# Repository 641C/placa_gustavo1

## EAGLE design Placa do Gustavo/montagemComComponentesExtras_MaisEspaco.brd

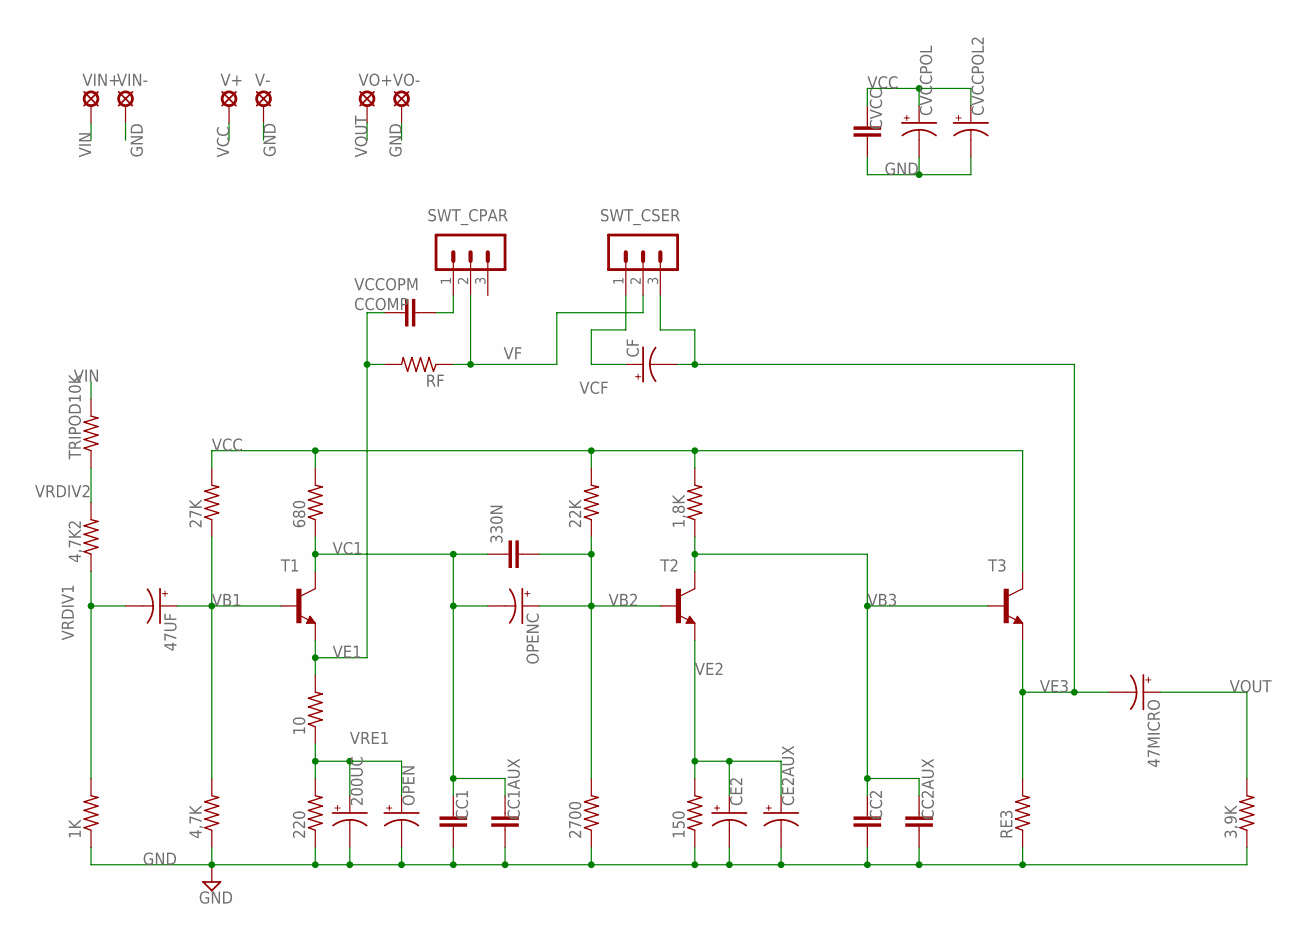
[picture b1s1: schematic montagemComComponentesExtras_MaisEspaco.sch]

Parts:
1,8K, 1K, 3,9K, 4,7K, 4,7K2, 10, 22K, 27K, 150, 220, 680, 2700: R-US_0207/10; 0207/10
47MICRO, 47UF, 200UC: CPOL-USE2.5-6; E2,5-6
330N: C-EU050-030X075; C050-030X075
CC1, CC1AUX, CC2, CC2AUX: C-EU050-030X075; C050-030X075
CCOMP: C-EU050-030X075; C050-030X075
CE2: CPOL-USE2.5-6; E2,5-6
CE2AUX: CPOL-USE5-8.5; E5-8,5
CF: CPOL-USE2.5-6; E2,5-6
CVCC: C-EU050-030X075; C050-030X075
CVCCPOL: CPOL-USE2.5-6; E2,5-6
CVCCPOL2: CPOL-USE5-8.5; E5-8,5
OPEN: CPOL-USE5-8.5; E5-8,5
OPENC: CPOL-USE2.5-6; E2,5-6
RE3: R-US_0207/10; 0207/10
RF: R-US_0207/10; 0207/10
SWT_CPAR: MA03-1
SWT_CSER: MA03-1
T1, T2, T3: BC368-NPN-TO92-ECB; TO92-ECB
TRIPOD10K: R-US_0207/10; 0207/10
V+: LSP10
V-: LSP10
VIN+: LSP10
VIN-: LSP10
VO+: LSP10
VO-: LSP10

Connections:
GND: 1K.1, 3,9K.1, 4,7K.1, 150.1, 200UC.-, 220.1, 2700.1, CC1.2, CC1AUX.2, CC2.2, CC2AUX.2, CE2.-, CE2AUX.-, CVCC.2, CVCCPOL.-, CVCCPOL2.-, OPEN.-, RE3.1, V-.MP, VIN-.MP, VO-.MP
VB1: 4,7K.2, 27K.1, 47UF.+, T1.B
VB2: 22K.1, 330N.2, 2700.2, OPENC.+, T2.B
VB3: 1,8K.1, CC2.1, CC2AUX.1, T2.C, T3.B
VC1: 330N.1, 680.1, CC1.1, CC1AUX.1, OPENC.-, T1.C
VCC: 1,8K.2, 22K.2, 27K.2, 680.2, CVCC.1, CVCCPOL.+, CVCCPOL2.+, T3.C, V+.MP
VCCOPM: CCOMP.2, SWT_CPAR.1
VCF: CF.+, SWT_CSER.1
VE1: 10.2, CCOMP.1, RF.2, T1.E
VE2: 150.2, CE2.+, CE2AUX.+, T2.E
VE3: 47MICRO.-, CF.-, RE3.2, SWT_CSER.3, T3.E
VF: RF.1, SWT_CPAR.2, SWT_CSER.2
VIN: TRIPOD10K.2, VIN+.MP
VOUT: 3,9K.2, 47MICRO.+, VO+.MP
VRDIV1: 1K.2, 4,7K2.1, 47UF.-
VRDIV2: 4,7K2.2, TRIPOD10K.1
VRE1: 10.1, 200UC.+, 220.2, OPEN.+

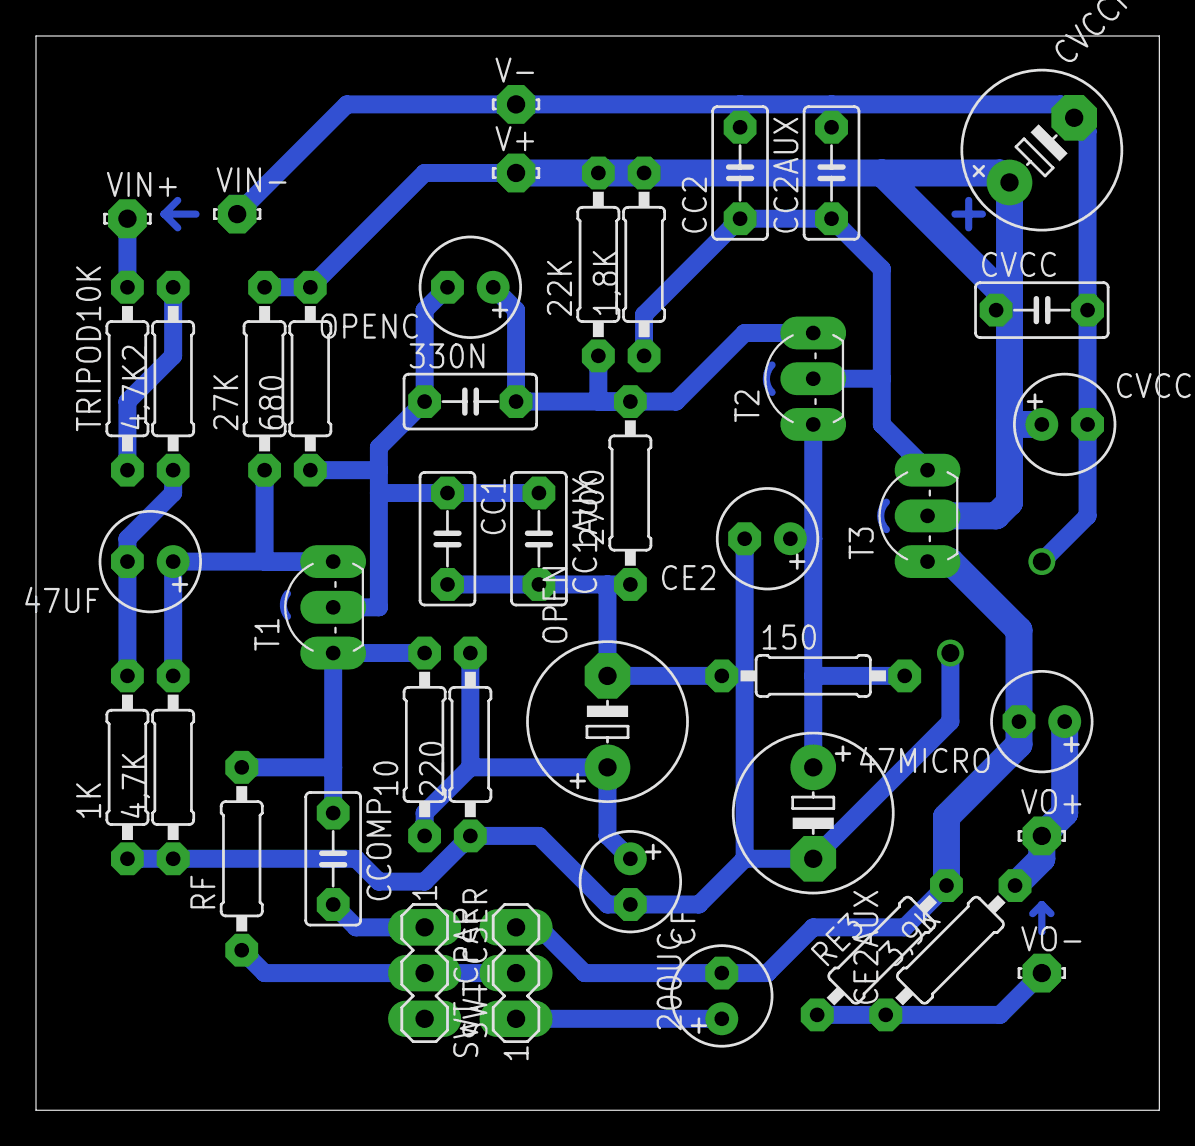
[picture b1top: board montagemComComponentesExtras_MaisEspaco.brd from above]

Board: 2 copper layers, 62.4 x 59.7 mm, 43 parts (0 on the bottom side), 17 nets.

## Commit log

2023-01-06 Primeiro Commit
